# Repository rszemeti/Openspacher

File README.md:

This badly written nonsense is my attempt at a controller to replace the one I found lurking in a Eberspacher D5S with a canbus interface for the Renault Master. It will eventuall provide a basic control protocol to allow it to be messed with over serial, N2K and probably just a simple on/off control input so you can use these units on boats etc without needing an entire Renault Master van in tow.

There is a PCB in Eagle too, kinda.

Please bear in mind it will probably set on fire, burn down your house, cause your cat to imnplode etc.

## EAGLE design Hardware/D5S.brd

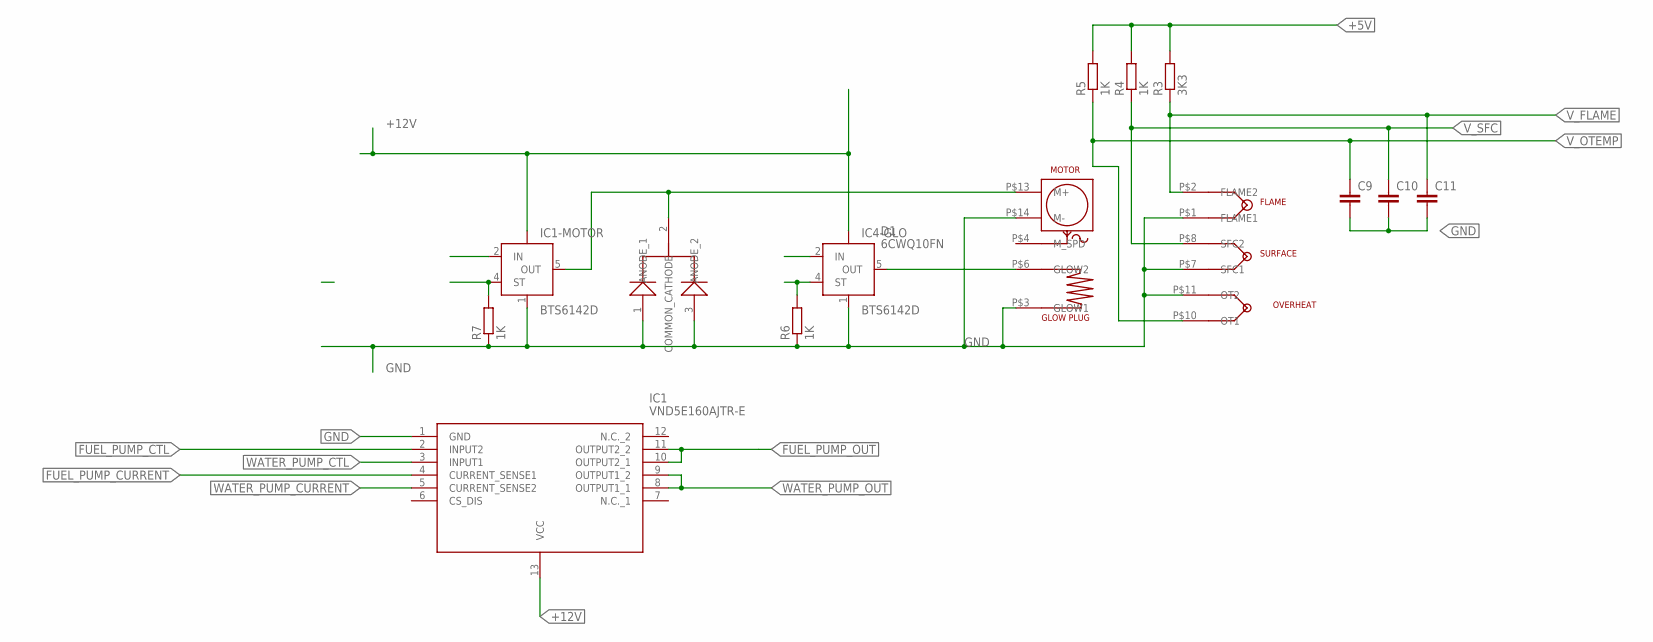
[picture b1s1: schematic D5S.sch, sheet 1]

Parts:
C9, C10, C11: C-EUC0603; C0603
D1: 6CWQ10FN
IC1: VND5E160AJTR-E; SOP80P600X162-13N
IC1-MOTOR, IC4-GLO: BTS6142D; TO252-5-11
R3: 3K3; R0603
R4, R5, R6, R7: 1K; R0603
U$1: D5S; PCB

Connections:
+5V: R3.2, R4.2, R5.2; also elsewhere on the board
+12V: IC1.13 (VCC), IC1-MOTOR.TAB (VBB), IC4-GLO.TAB (VBB)
FAN_CTL: IC1-MOTOR.2 (IN); also elsewhere on the board
FAN_SENSE: IC1-MOTOR.4 (ST), R7.2
FUEL_PUMP_CTL: IC1.2 (INPUT2); also elsewhere on the board
FUEL_PUMP_CURRENT: IC1.4 (CURRENT_SENSE1)
FUEL_PUMP_OUT: IC1.10 (OUTPUT2_1), IC1.11 (OUTPUT2_2)
GLOW_CTL: IC4-GLO.2 (IN); also elsewhere on the board
GLOW_SENSE: IC4-GLO.4 (ST), R6.2
GND: C9.2, C10.2, C11.2, D1.1 (ANODE_1), D1.3 (ANODE_2), IC1.1 (GND), IC1-MOTOR.1 (GND), IC4-GLO.1 (GND), R6.1, R7.1, U$1.P$1 (FLAME1), U$1.P$3 (GLOW1), U$1.P$7 (SFC1), U$1.P$11 (OT2), U$1.P$14 (M-); also elsewhere on the board
unnamed: IC4-GLO.5 (OUT), U$1.P$6 (GLOW2)
unnamed: D1.2 (COMMON_CATHODE), IC1-MOTOR.5 (OUT), U$1.P$13 (M+)
V_FLAME: C11.1, R3.1, U$1.P$2 (FLAME2); also elsewhere on the board
V_OTEMP: C9.1, R5.1, U$1.P$10 (OT1); also elsewhere on the board
V_SFC: C10.1, R4.1, U$1.P$8 (SFC2); also elsewhere on the board
WATER_PUMP_CTL: IC1.3 (INPUT1); also elsewhere on the board
WATER_PUMP_CURRENT: IC1.5 (CURRENT_SENSE2)
WATER_PUMP_OUT: IC1.8 (OUTPUT1_1), IC1.9 (OUTPUT1_2)

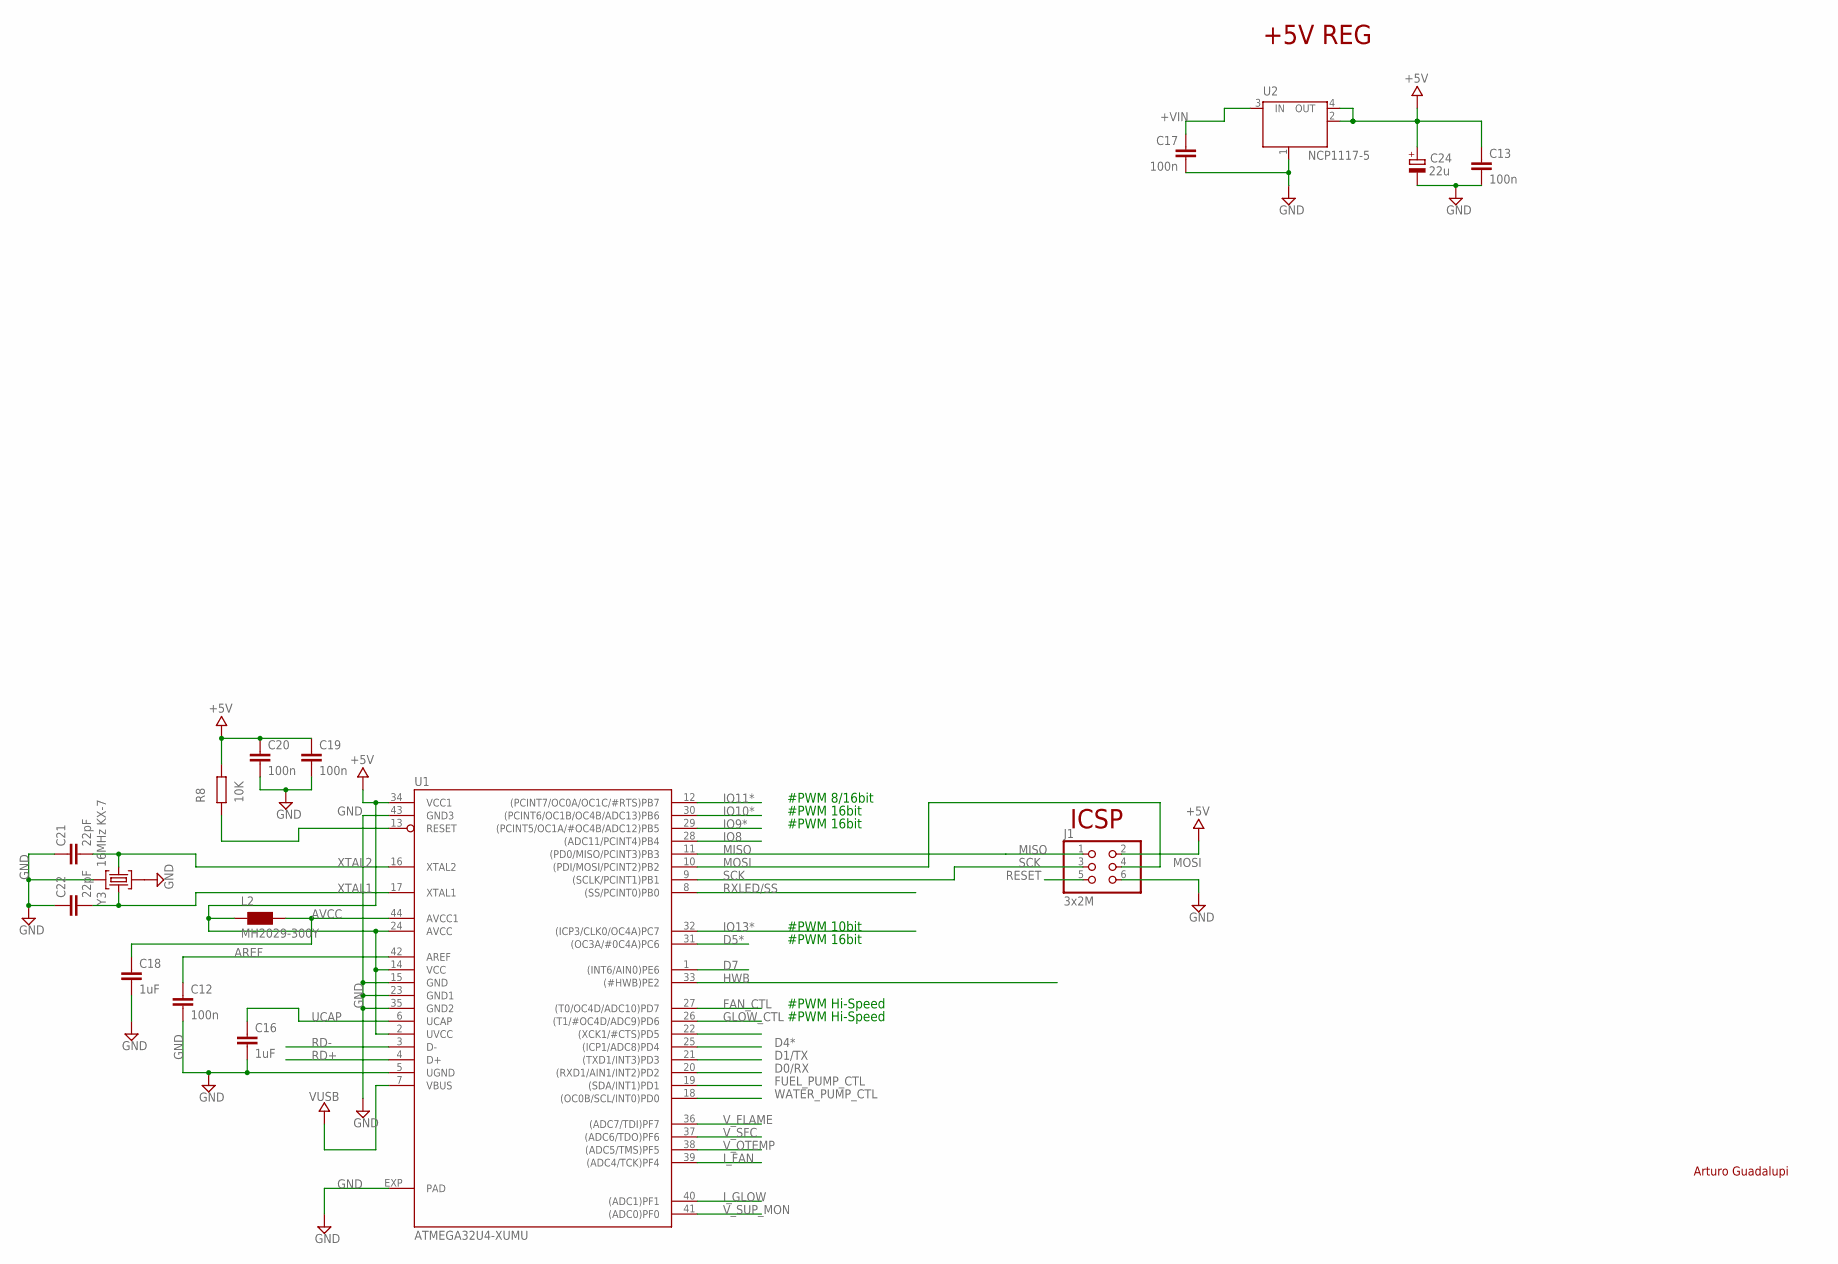
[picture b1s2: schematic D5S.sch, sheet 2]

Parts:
C12, C13, C17, C19, C20: 100n; C0402
C16, C18: 1uF; C0402
C21, C22: 22pF; C0402
C24: 22u; SMC_B
J1: 3x2M; 2X03
L2: MH2029-300Y; 0805
R8: 10K; R0402
U1: ATMEGA32U4-XUMU; QFN44ML7X7
U2: NCP1117-5; SOT223
Y3: 16MHz KX-7; CRYSTAL-3.2-2.5

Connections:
+5V: C13.1, C19.1, C20.1, C24.+, J1.2, L2.1, R8.1, U1.2 (UVCC), U1.14 (VCC), U1.24 (AVCC), U1.34 (VCC1), U2.2 (OUT), U2.4 (OUT); also elsewhere on the board
+VIN: C17.1, U2.3 (IN)
AREF: C12.1, U1.42 (AREF)
AVCC: C18.1, L2.2, U1.44 (AVCC1)
D0/RX: U1.20 ((RXD1/AIN1/INT2)PD2)
D1/TX: U1.21 ((TXD1/INT3)PD3)
D4*: U1.25 ((ICP1/ADC8)PD4)
D5*: U1.31 ((OC3A/#0C4A)PC6)
D7: U1.1 ((INT6/AIN0)PE6)
FAN_CTL: U1.27 ((T0/OC4D/ADC10)PD7); also elsewhere on the board
FUEL_PUMP_CTL: U1.19 ((SDA/INT1)PD1); also elsewhere on the board
GLOW_CTL: U1.26 ((T1/#OC4D/ADC9)PD6); also elsewhere on the board
GND: C12.2, C13.2, C16.2, C17.2, C18.2, C19.2, C20.2, C21.1, C22.1, C24.-, J1.6, U1.5 (UGND), U1.15 (GND), U1.23 (GND1), U1.35 (GND2), U1.43 (GND3), U1.EXP (PAD), U2.1 (GND/ADJ), Y3.2 (GND), Y3.4 (GND); also elsewhere on the board
HWB: U1.33 ((#HWB)PE2)
IO8: U1.28 ((ADC11/PCINT4)PB4)
IO9*: U1.29 ((PCINT5/OC1A/#OC4B/ADC12)PB5)
IO10*: U1.30 ((PCINT6/OC1B/OC4B/ADC13)PB6)
IO11*: U1.12 ((PCINT7/OC0A/OC1C/#RTS)PB7)
IO13*: U1.32 ((ICP3/CLK0/OC4A)PC7)
I_FAN: U1.39 ((ADC4/TCK)PF4)
I_GLOW: U1.40 ((ADC1)PF1)
MISO: J1.1, U1.11 ((PD0/MISO/PCINT3)PB3)
MOSI: J1.4, U1.10 ((PDI/MOSI/PCINT2)PB2)
RD+: U1.4 (D+)
RD-: U1.3 (D-)
RESET: J1.5, R8.2, U1.13 (RESET)
RXLED/SS: U1.8 ((SS/PCINT0)PB0)
SCK: J1.3, U1.9 ((SCLK/PCINT1)PB1)
TXLED: U1.22 ((XCK1/#CTS)PD5)
UCAP: C16.1, U1.6 (UCAP)
VUSB: U1.7 (VBUS)
V_FLAME: U1.36 ((ADC7/TDI)PF7); also elsewhere on the board
V_OTEMP: U1.38 ((ADC5/TMS)PF5); also elsewhere on the board
V_SFC: U1.37 ((ADC6/TDO)PF6); also elsewhere on the board
V_SUP_MON: U1.41 ((ADC0)PF0)
WATER_PUMP_CTL: U1.18 ((OC0B/SCL/INT0)PD0); also elsewhere on the board
XTAL1: C22.2, U1.17 (XTAL1), Y3.3 (C2)
XTAL2: C21.2, U1.16 (XTAL2), Y3.1 (C1)

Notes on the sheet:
+5V REG
ICSP
#PWM Hi-Speed
#PWM 16bit
#PWM 10bit
#PWM 8/16bit
Arturo Guadalupi

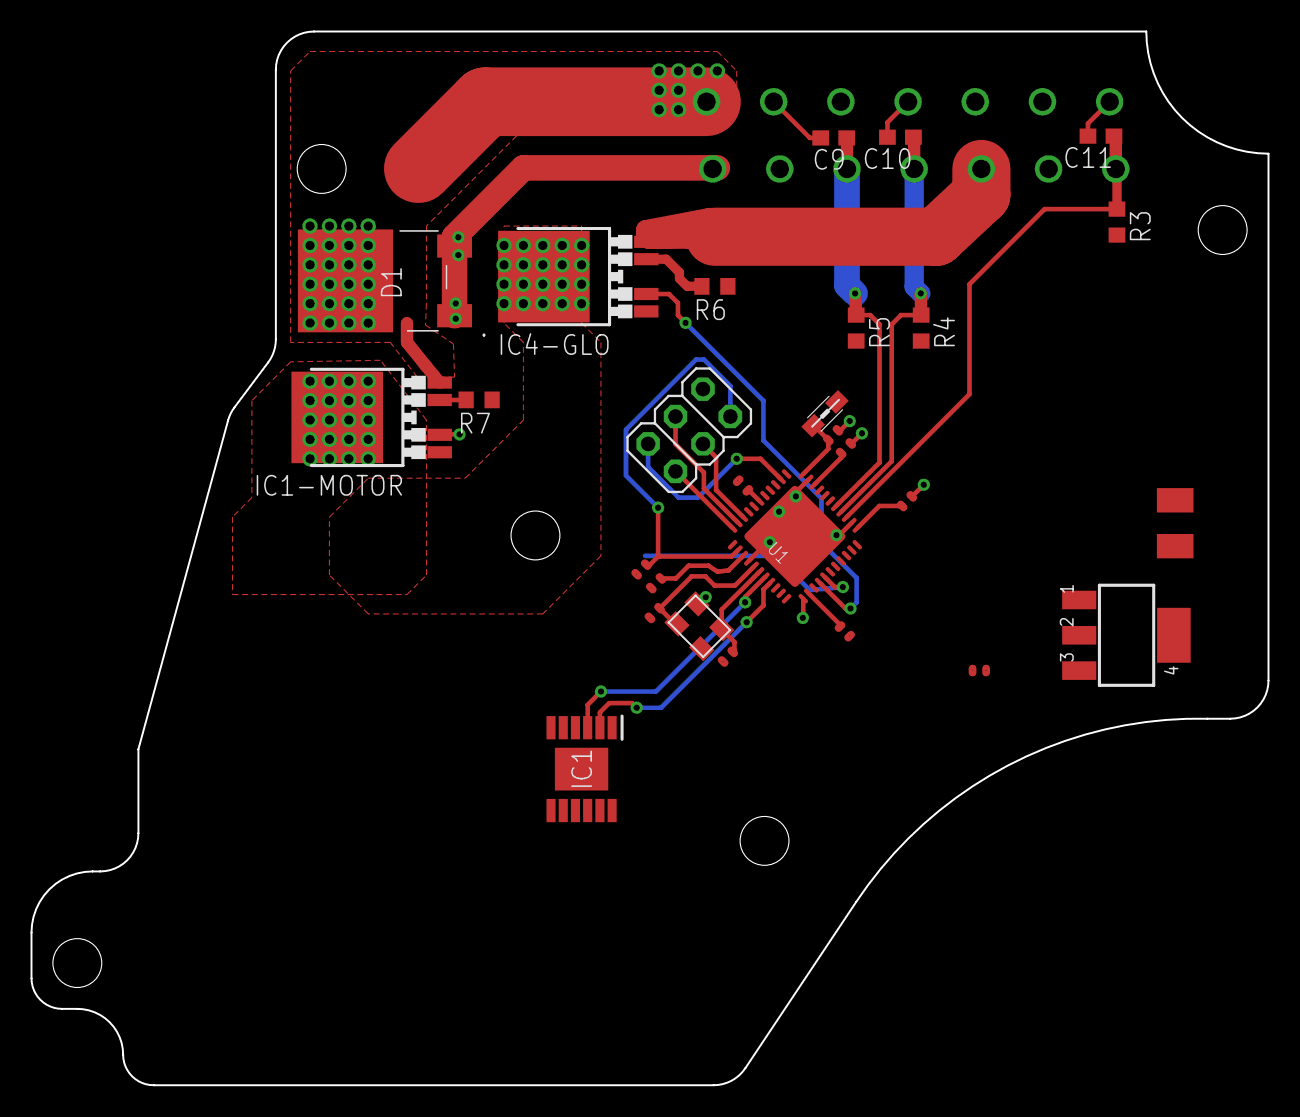
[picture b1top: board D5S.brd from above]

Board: 4 copper layers, 81.0 x 69.0 mm, 29 parts (0 on the bottom side), 26 nets.

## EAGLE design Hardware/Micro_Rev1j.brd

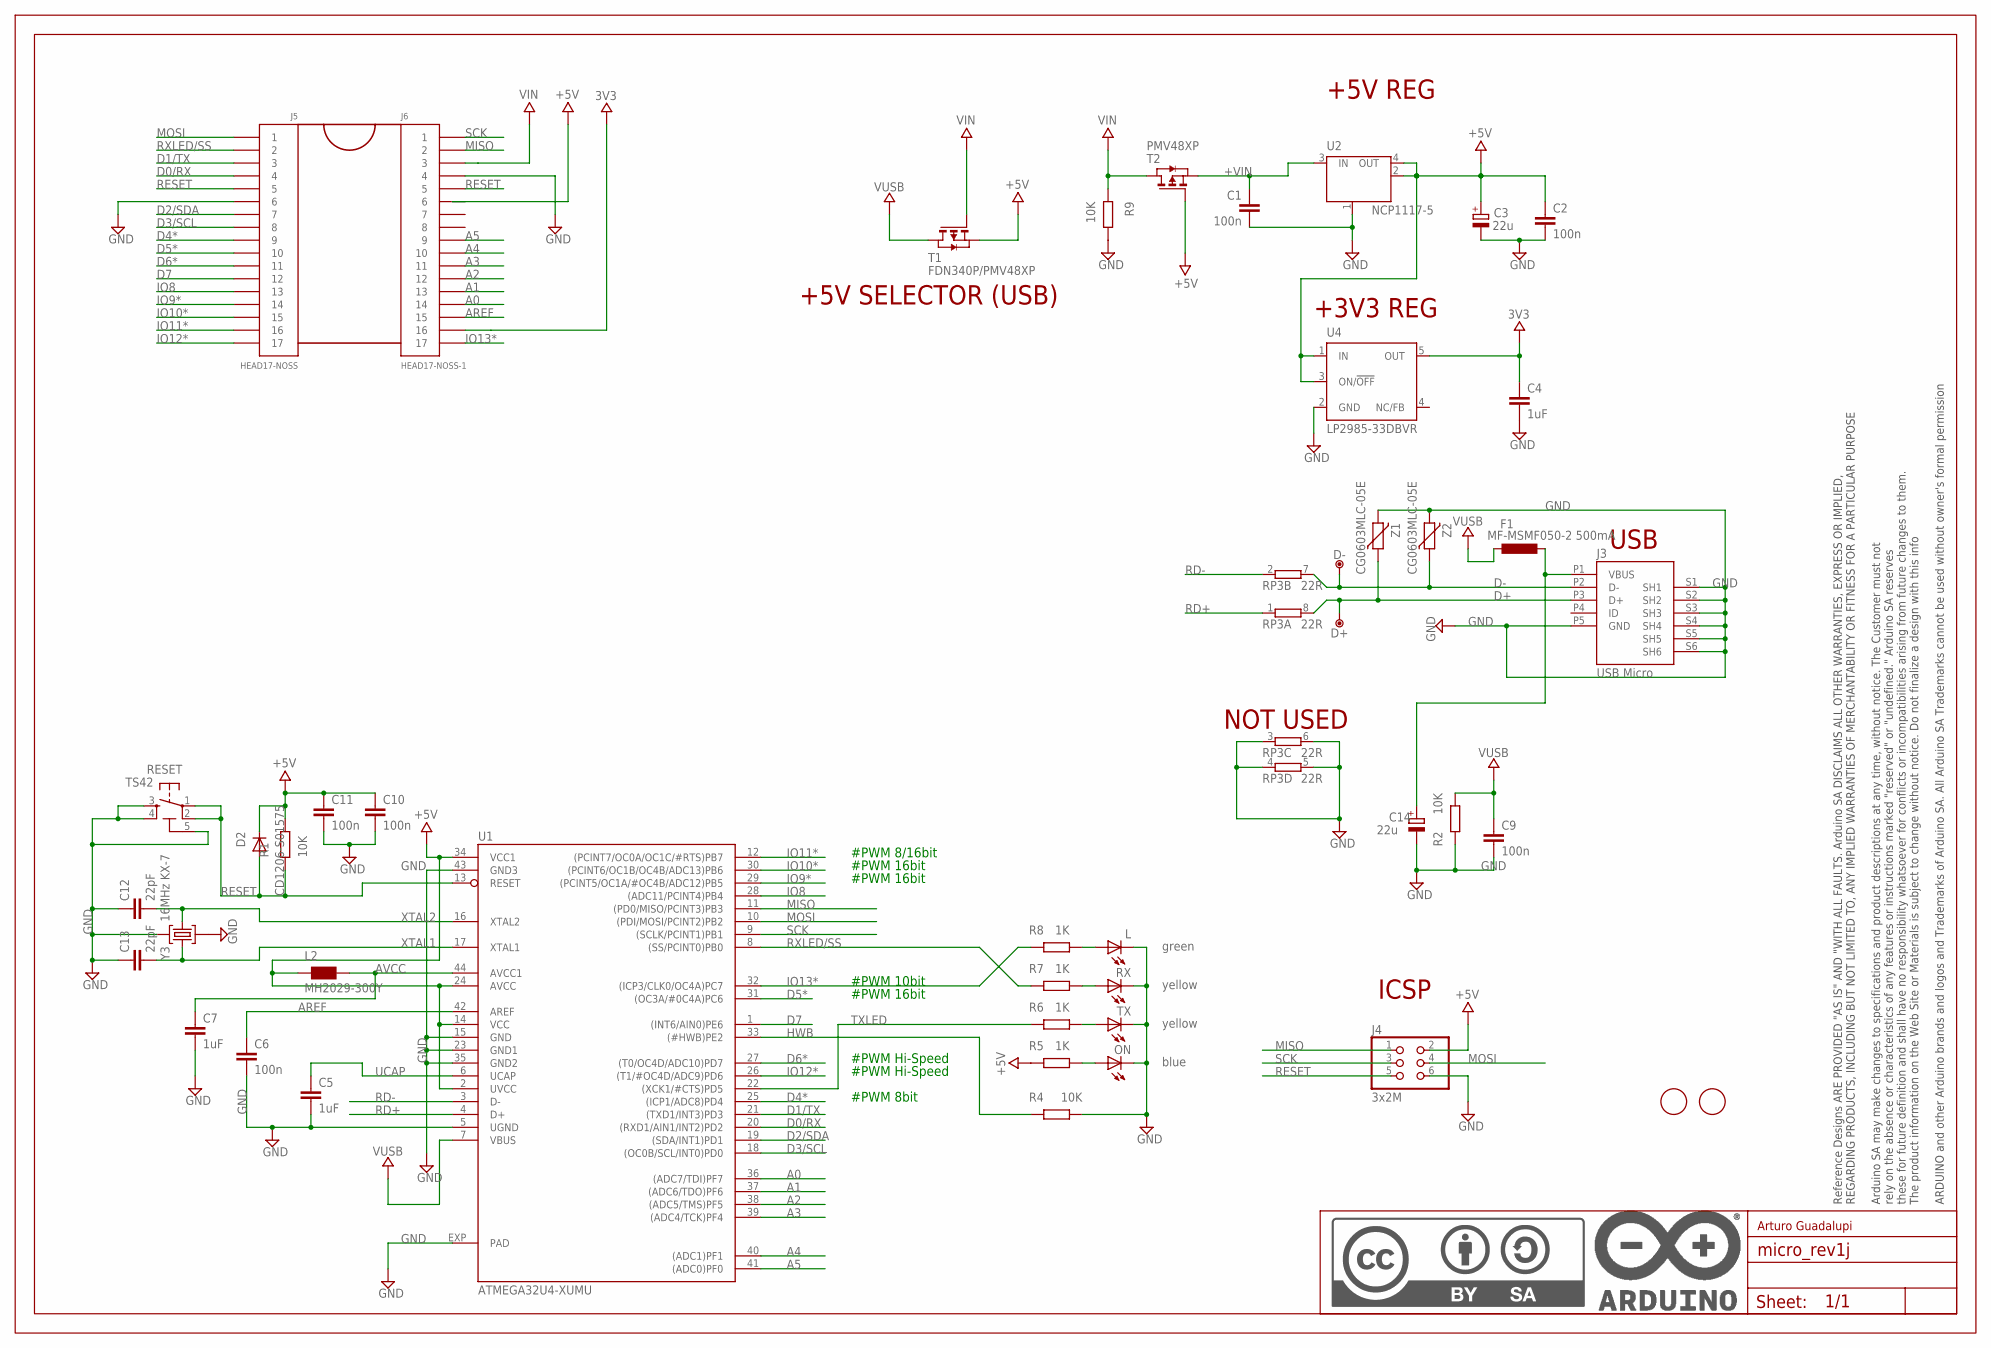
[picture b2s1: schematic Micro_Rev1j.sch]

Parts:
C1, C2, C6, C9, C10, C11: 100n; C0402
C3, C14: 22u; SMC_B
C4, C5, C7: 1uF; C0402
C12, C13: 22pF; C0402
D2: CD1206-S01575; MINIMELF
D+: DNP; TP-1.00MM
D-: DNP; TP-1.00MM
F1: MF-MSMF050-2 500mA; L1812
FRAME1: DNP; FRAME
J3: USB Micro; CON2_USB_MICRO_B_AT
J4: 3x2M; 2X03
J5: HEAD17-NOSS
J6: HEAD17-NOSS-1
L: green; CHIPLED_0805
L2: MH2029-300Y; 0805
ON: blue; CHIPLED_0805
R1, R2, R4, R9: 10K; R0402
R5, R6, R7, R8: 1K; R0402
RESET: TS42
RP3: 22R; CAY16
RX: yellow; CHIPLED_0805
T1: FDN340P/PMV48XP; SOT-23
T2: PMV48XP; SOT-23
TX: yellow; CHIPLED_0805
U1: ATMEGA32U4-XUMU; QFN44ML7X7
U2: NCP1117-5; SOT223
U4: LP2985-33DBVR; SOT23-DBV
U$37, U$53: DNP; FD-1-1.5
Y3: 16MHz KX-7; CRYSTAL-3.2-2.5
Z1, Z2: CG0603MLC-05E; CT/CN0603

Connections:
3V3: C4.1, J6.16, U4.5 (OUT)
+5V: C2.1, C3.+, C10.1, C11.1, D2.C, J4.2, J6.6, L2.1, R1.1, R5.1, T1.2 (S), T2.3 (G), U1.2 (UVCC), U1.14 (VCC), U1.24 (AVCC), U1.34 (VCC1), U2.2 (OUT), U2.4 (OUT), U4.1 (IN), U4.3 (ON/!OFF)
+VIN: C1.1, T2.2 (S), U2.3 (IN)
A0: J6.14, U1.36 ((ADC7/TDI)PF7)
A1: J6.13, U1.37 ((ADC6/TDO)PF6)
A2: J6.12, U1.38 ((ADC5/TMS)PF5)
A3: J6.11, U1.39 ((ADC4/TCK)PF4)
A4: J6.10, U1.40 ((ADC1)PF1)
A5: J6.9, U1.41 ((ADC0)PF0)
AREF: C6.1, J6.15, U1.42 (AREF)
AVCC: C7.1, L2.2, U1.44 (AVCC1)
D0/RX: J5.4, U1.20 ((RXD1/AIN1/INT2)PD2)
D1/TX: J5.3, U1.21 ((TXD1/INT3)PD3)
D2/SDA: J5.7, U1.19 ((SDA/INT1)PD1)
D3/SCL: J5.8, U1.18 ((OC0B/SCL/INT0)PD0)
D4*: J5.9, U1.25 ((ICP1/ADC8)PD4)
D5*: J5.10, U1.31 ((OC3A/#0C4A)PC6)
D6*: J5.11, U1.27 ((T0/OC4D/ADC10)PD7)
D7: J5.12, U1.1 ((INT6/AIN0)PE6)
D+: D+.X, J3.P3 (D+), RP3.8 (2), Z1.1
D-: D-.X, J3.P2 (D-), RP3.7 (2), Z2.1
GND: C1.2, C2.2, C3.-, C4.2, C5.2, C6.2, C7.2, C9.2, C10.2, C11.2, C12.1, C13.1, C14.-, J3.P5 (GND), J3.S1 (SH1), J3.S2 (SH2), J3.S3 (SH3), J3.S4 (SH4), J3.S5 (SH5), J3.S6 (SH6), J4.6, J5.6, J6.4, L.C, ON.C, R2.1, R4.2, R9.1, RESET.3, RESET.4, RESET.5 (5-GND), RP3.3 (1), RP3.4 (1), RP3.5 (2), RP3.6 (2), RX.C, TX.C, U1.5 (UGND), U1.15 (GND), U1.23 (GND1), U1.35 (GND2), U1.43 (GND3), U1.EXP (PAD), U2.1 (GND/ADJ), U4.2 (GND), Y3.2 (GND), Y3.4 (GND), Z1.2, Z2.2
HWB: R4.1, U1.33 ((#HWB)PE2)
IO8: J5.13, U1.28 ((ADC11/PCINT4)PB4)
IO9*: J5.14, U1.29 ((PCINT5/OC1A/#OC4B/ADC12)PB5)
IO10*: J5.15, U1.30 ((PCINT6/OC1B/OC4B/ADC13)PB6)
IO11*: J5.16, U1.12 ((PCINT7/OC0A/OC1C/#RTS)PB7)
IO12*: J5.17, U1.26 ((T1/#OC4D/ADC9)PD6)
IO13*: J6.17, R8.1, U1.32 ((ICP3/CLK0/OC4A)PC7)
MISO: J4.1, J6.2, U1.11 ((PD0/MISO/PCINT3)PB3)
MOSI: J4.4, J5.1, U1.10 ((PDI/MOSI/PCINT2)PB2)
unnamed: R7.2, RX.A
unnamed: ON.A, R5.2
unnamed: R6.2, TX.A
unnamed: L.A, R8.2
RD+: RP3.1, U1.4 (D+)
RD-: RP3.2 (1), U1.3 (D-)
RESET: D2.A, J4.5, J5.5, J6.5, R1.2, RESET.1, RESET.2, U1.13 (RESET)
RXLED/SS: J5.2, R7.1, U1.8 ((SS/PCINT0)PB0)
SCK: J4.3, J6.1, U1.9 ((SCLK/PCINT1)PB1)
TXLED: R6.1, U1.22 ((XCK1/#CTS)PD5)
UCAP: C5.1, U1.6 (UCAP)
VIN: J6.3, R9.2, T1.3 (G), T2.1 (D)
VUSB: C9.1, F1.2, R2.2, T1.1 (D), U1.7 (VBUS)
VUSBD: C14.+, F1.1, J3.P1 (VBUS)
XTAL1: C13.2, U1.17 (XTAL1), Y3.3 (C2)
XTAL2: C12.2, U1.16 (XTAL2), Y3.1 (C1)

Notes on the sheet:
+5V REG
ICSP
USB
+5V SELECTOR (USB)
NOT USED
+3V3 REG
#PWM 8bit
#PWM Hi-Speed
#PWM 16bit
#PWM 10bit
#PWM 8/16bit
Arturo Guadalupi

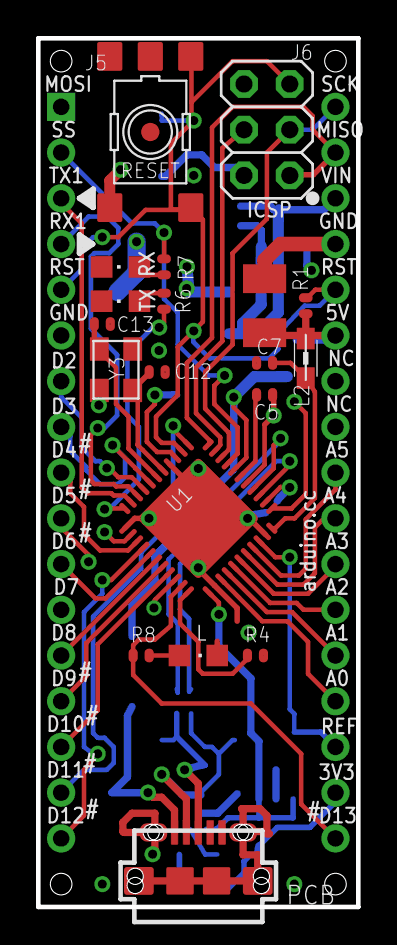
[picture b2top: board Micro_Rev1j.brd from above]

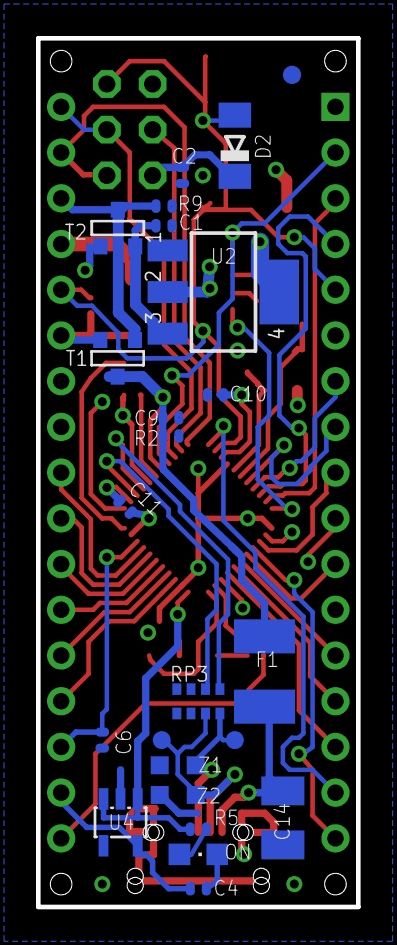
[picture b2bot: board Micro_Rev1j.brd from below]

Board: 4 copper layers, 17.8 x 48.3 mm, 47 parts (22 on the bottom side), 47 nets.

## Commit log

2024-12-03 Initial
2024-12-03 Stuff from laptop
2024-12-04 Statemachin implemetation in Python for testing
2024-12-06 refinements!
2024-12-06 Arduino initial transplation from Python statemachine
2024-12-08 Interpolation and better structure to define the stages
    All the various tage timing etc is in the header . file, just dummy data for now.
2024-12-08 Further tweakage
    Runtimes and sequences now correct from D5 manual
2024-12-08 Closer ...
2024-12-08 help functions update
    end stage handlers updated

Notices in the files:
Hardware/Micro_Rev1j.brd:
Copyright (c) 2016-2017 Arduino LLC.  All right reserved. EAGLE Design Rules
parts and their libraries:
Arduino-utility: Copyright (c) 2016-2017 Arduino LLC.  All right reserved.
